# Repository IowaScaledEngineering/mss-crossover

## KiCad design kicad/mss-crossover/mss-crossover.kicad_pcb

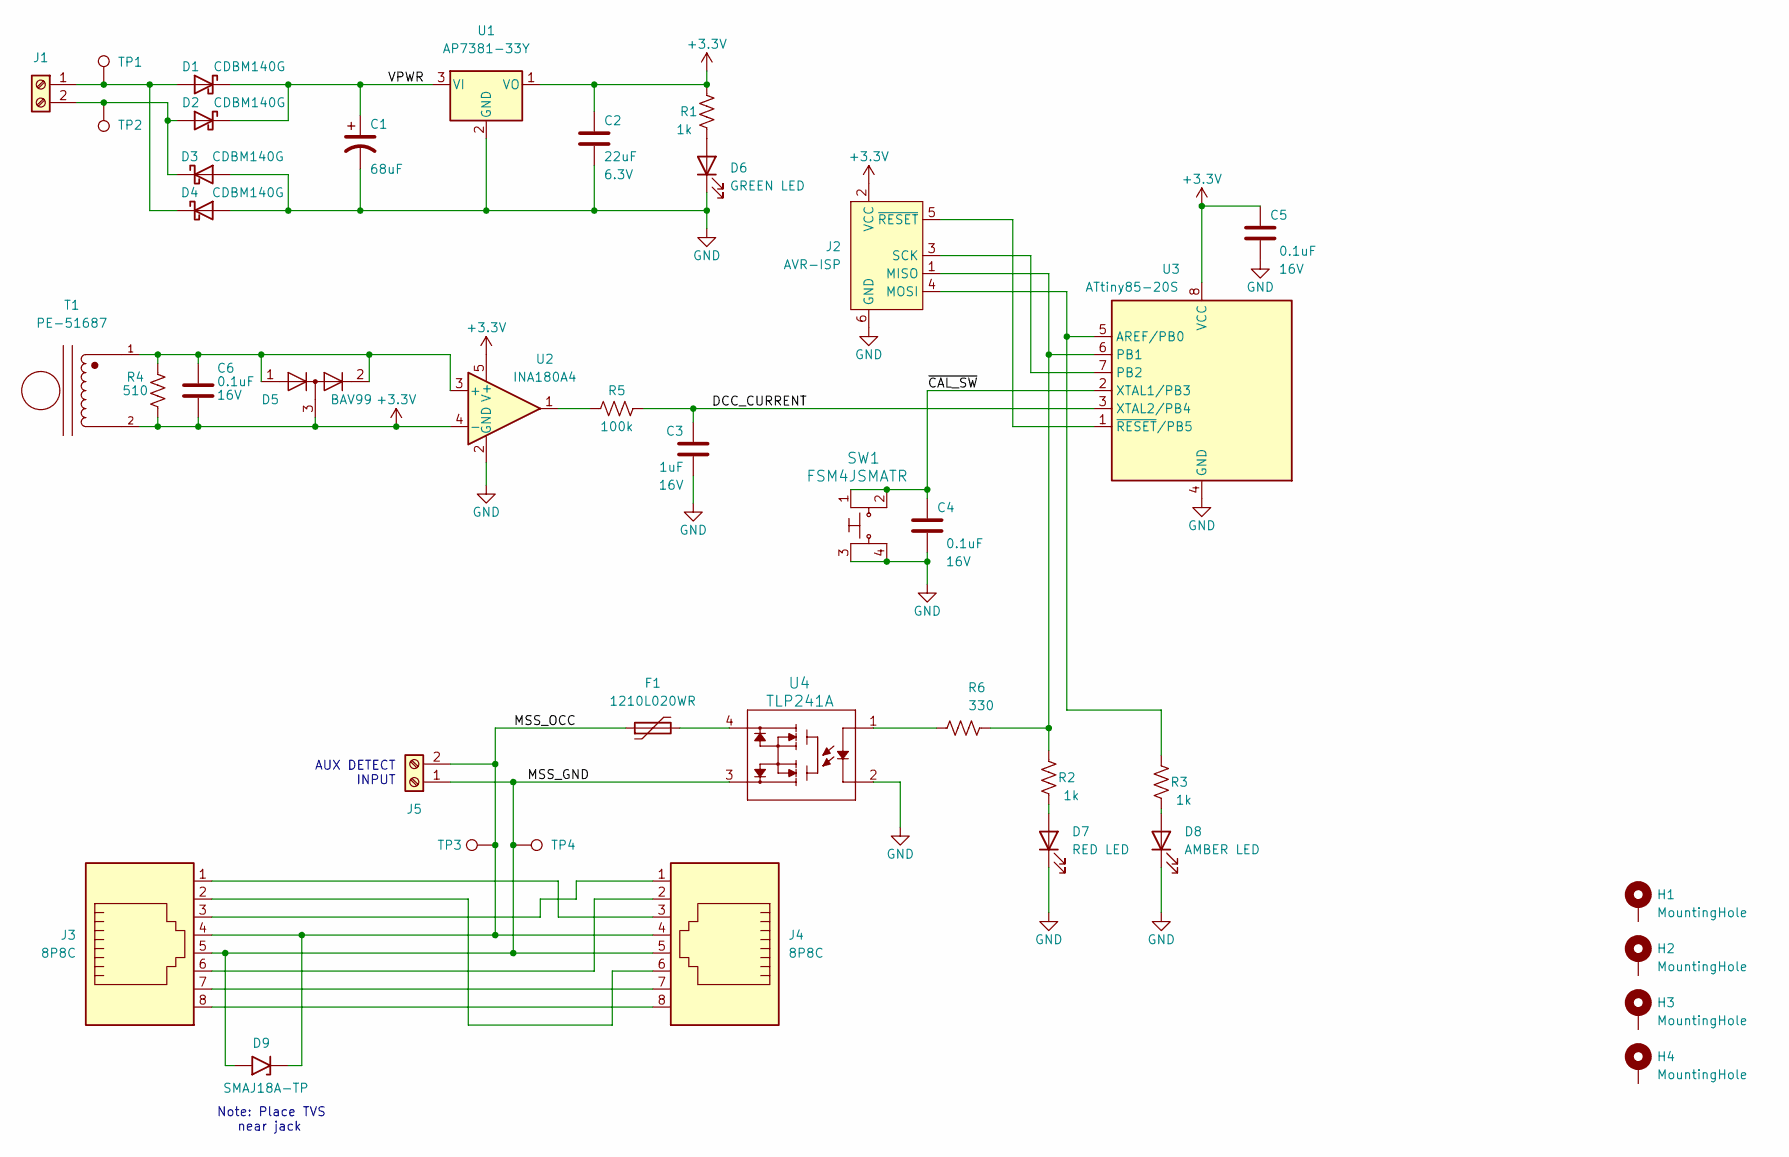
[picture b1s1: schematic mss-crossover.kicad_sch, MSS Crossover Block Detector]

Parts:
C1: 68uF; CP_Elec_6.3x5.8
C2: 22uF; C_0805_2012Metric; Voltage 6.3V
C3: 1uF; C_0805_2012Metric; Voltage 16V
C4, C5, C6: 0.1uF; C_0805_2012Metric; Voltage 16V
D1, D2, D3, D4: CDBM140G; SOD-123T
D5: BAV99; SOT-23
D6: GREEN LED; LED_0805_2012Metric
D7: RED LED; LED_0805_2012Metric
D8: AMBER LED; LED_0805_2012Metric
D9: SMAJ18A-TP; D_SMA
F1: 1210L020WR; R_1210_3225Metric
H1, H2, H3, H4: MountingHole; MountingHole_3.2mm_M3_Pad
J1, J5: Screw_Terminal_01x02; TerminalBlock_RND_205-00012_1x02_P5.00mm_Horizontal
J2: AVR-ISP; Tag-Connect_TC2030-IDC-NL_2x03_P1.27mm_Vertical
J3, J4: 8P8C; RJ45_Amphenol_54602-x08_Horizontal
R1, R2, R3: 1k; R_0805_2012Metric
R4: 510; R_0805_2012Metric
R5: 100k; R_0805_2012Metric
R6: 330; R_0805_2012Metric
SW1: FSM4JSMATR; TE_FSM4JSMA; MPN FSM4JSMATR; Digi-Key_PN 450-1759-1-ND
T1: PE-51687; XFMR_PE-51687
TP1, TP2, TP3, TP4: TestPoint; TestPoint_Pad_D2.0mm
U1: AP7381-33Y; SOT-89-3
U2: INA180A4; SOT-23-5
U3: ATtiny85-20S; ATMEL_SO8_DUAL
U4: TLP241A; 11-5B201S_TOS

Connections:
+3.3V: C2.1, C5.1, C6.2, D5.3 (K), J2.2 (VCC), R1.2, R4.1, T1.2, U1.1 (VO), U2.4 (-), U2.5 (V+), U3.8 (VCC)
/DCC_CURRENT: C3.1, R5.1, U3.3 (XTAL2/PB4)
/MSS_GND: D9.2 (A2), J3.5, J4.5, J5.1, TP4.1, U4.3
/MSS_OCC: D9.1 (A1), F1.1, J3.4, J4.4, J5.2, TP3.1
/VPWR: C1.1, D1.1 (K), D2.1 (K), U1.3 (VI)
/~CAL_SW: C4.1, SW1.1, SW1.2, U3.2 (XTAL1/PB3)
GND: C1.2, C2.2, C3.2, C4.2, C5.2, D3.2 (A), D4.2 (A), D6.1 (K), D7.1 (K), D8.1 (K), J2.6 (GND), SW1.3, SW1.4, U1.2 (GND), U2.2 (GND), U3.4 (GND), U4.2
unnamed: C6.1, D5.1 (K), D5.2 (A), R4.2, T1.1, U2.3 (+)
unnamed: D1.2 (A), D4.1 (K), J1.1, TP1.1
unnamed: D2.2 (A), D3.1 (K), J1.2, TP2.1
unnamed: D6.2 (A), R1.1
unnamed: D7.2 (A), R2.2
unnamed: D8.2 (A), R3.2
unnamed: F1.2, U4.4
unnamed: J2.1 (MISO), R2.1, R6.2, U3.6 (PB1)
unnamed: J2.3 (SCK), U3.7 (PB2)
unnamed: J2.4 (MOSI), R3.1, U3.5 (AREF/PB0)
unnamed: J2.5 (~RESET), U3.1 (~RESET/PB5)
unnamed: J3.1, J4.3
unnamed: J3.2, J4.6
unnamed: J3.3, J4.1
unnamed: J3.6, J4.2
unnamed: J3.7, J4.7
unnamed: J3.8, J4.8
unnamed: R5.2, U2.1
unnamed: R6.1, U4.1

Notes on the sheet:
AUX DETECT INPUT
Note: Place TVS near jack

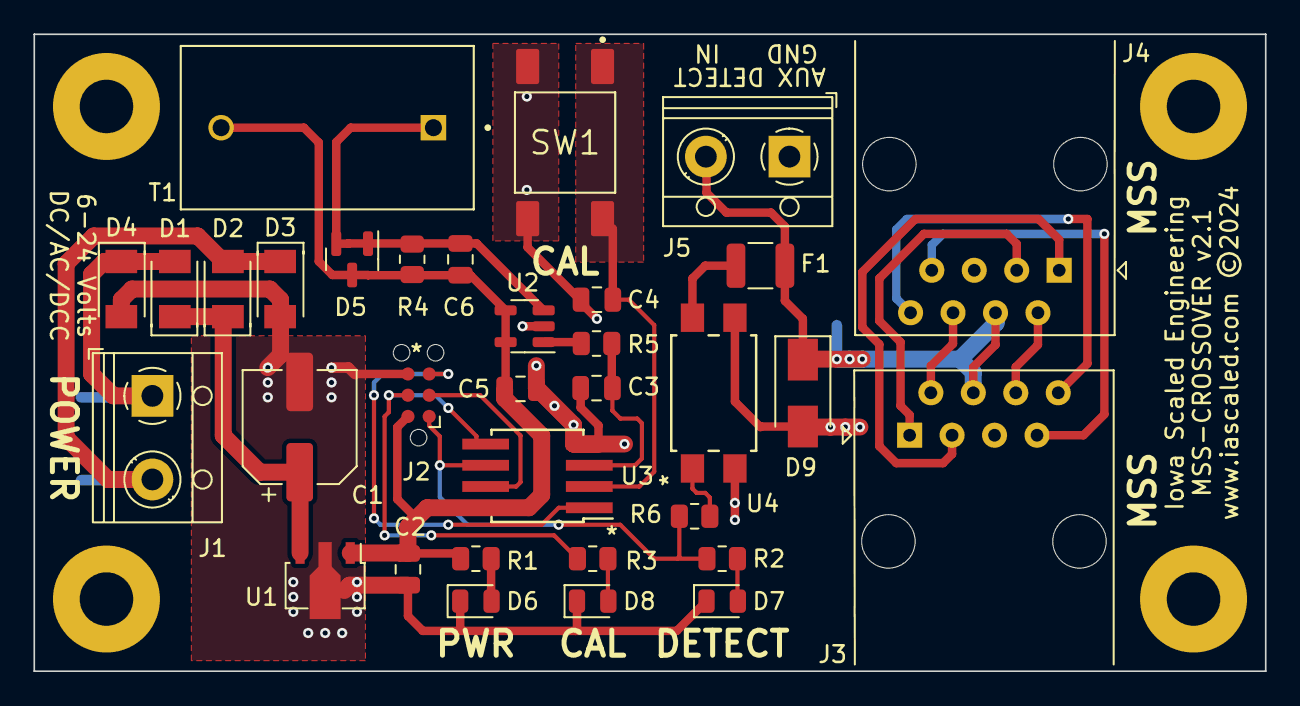
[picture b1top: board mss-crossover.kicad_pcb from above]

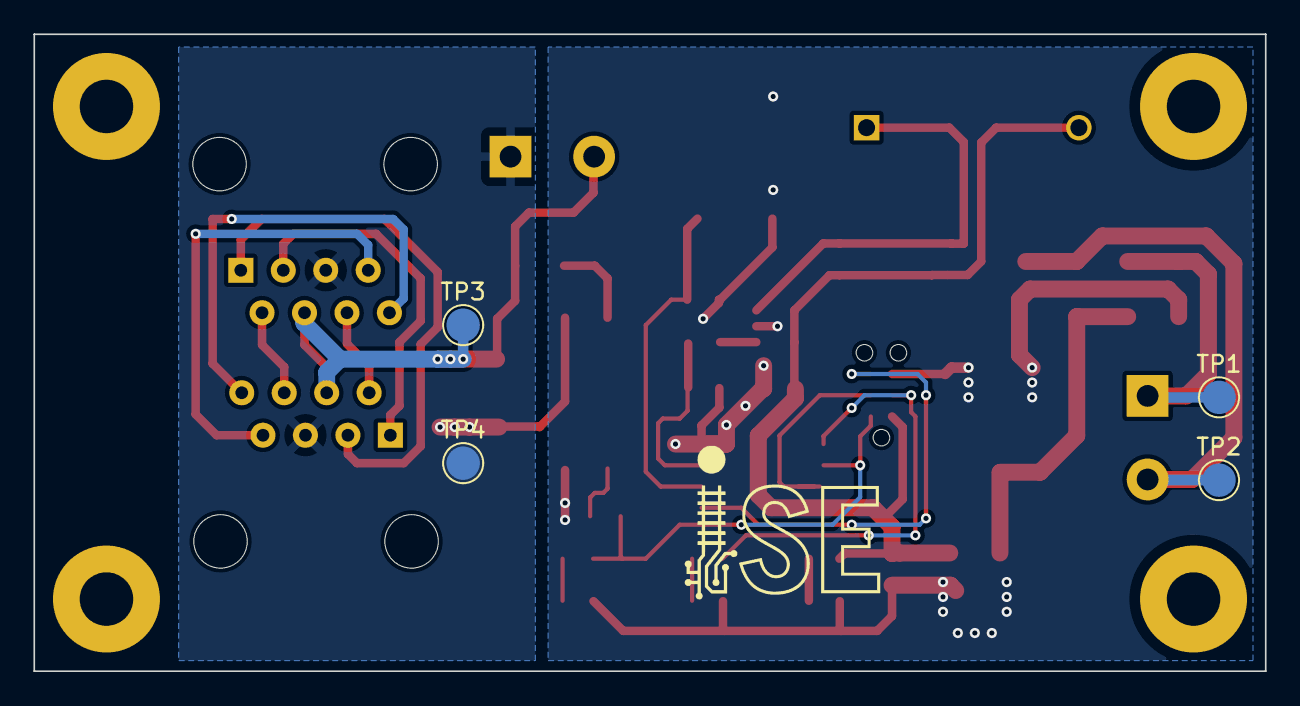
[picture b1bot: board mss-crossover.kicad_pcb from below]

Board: 2 copper layers, 73.7 x 38.1 mm, 41 parts (4 on the bottom side), 26 nets.

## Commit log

2015-10-14 Initial cut of mss-crossover module
2015-10-14 Add licensing, update gitignore
2015-10-14 Update text on schematic
2015-10-27 Change micro, add occupancy input (for turnouts, etc.) and clean up a few things
2015-10-28 First cut of "finished" pcb
2015-10-28 Update occupancy input pullup resistor value
2015-10-28 Twiddling with refdes cleanup and other last minute stuff
2015-11-02 Fix a few things from Michael's review.
2015-11-02 Remove a tiny metal sliver
2015-11-03 Add sensitivity adjustment guide text
2015-11-03 PG v1.0
2015-11-20 Add src
2015-11-21 Diagram for user manual
2015-11-21 Removed extraneous wires
2015-11-21 Add preliminary manual work
2015-11-21 First attempt
2015-11-22 Add blink on aux input functionality
2015-11-22 Reverse light pin definitions
2015-11-23 Change to read delays from eeprom and update if needed
2015-11-24 More manual editing
2015-11-24 Suggestions from Gregg F: - clamp on the aux input - jumper MSS bus 7 to MSS ground, allowing for use as an alternate function
2015-11-24 Modify schematic to add comment Modify PCB to add JP1 and Q2
2015-11-25 Move R10 to the back side of the protection fet to inhibit backfeeding into the power rail
2016-02-26 Add documentation about JP1
2016-03-01 Fix a few things in the manual and make it 1.0
2016-03-06 Make the 1Hz blink actually 1Hz
2016-03-06 Update gitignore to ignore build intermediates
2016-09-14 Change out input protection circuit for a new one.
2016-09-14 Fix a bit of missing metal plane in lower right
2016-09-14 Add schottky symbol
2016-09-14 Combine R6/R9 into 100k 2-pack
2016-09-17 Add crossover v1.1
2017-06-02 Decreased solder paste aperature on the QFN32 footprint. Bumped rev to 1.2 Changed (C) to 2017
2017-06-02 Decreased QFN paste aperture
2017-06-15 Added bag top
2017-09-12 Added new ISE logo.
2018-12-13 Potential v1.3 candidate - improved detector, some other simplifications
2018-12-27 Add pushbutton for DCC current auto-set
2018-12-30 Sent to Seeed
2019-01-14 Fix slot attributes
2019-04-04 New firmware for pushbutton current set
2019-04-04 Change the default current value to approximately what a 10k resistor comes up to on my test track
2024-02-15 New MSS-CROSSOVER v2.0 in Kicad
2024-02-17 Initial PCB layout complete on v2.0
2024-02-25 Updates per review
2024-04-03 Add test points
2024-04-03 Add 3d models
2024-04-06 Files for fab
2024-05-20 Update footprints for AVR to allow for both narrow/wide SO8s and footprint for CDBMs to allow for more paste
2024-05-21 Fix dual footprint SO8
2024-05-21 Update schematic footprints from PCB changes
2024-05-21 Remove old source code and schematic/pcb files from geda
2024-05-21 Fix diode spacing to appease McFussyPants
2024-05-24 Add auxilliary detection terminal block
2024-05-26 Move transformer over and center switch to give more finger room Label aux detect terminals for GND and IN
2024-05-29 Add v4.1 array
2024-05-29 PG of mss-crossover v2.1 array
2024-07-02 Removed old MSS documentation
2024-07-02 Updated ignores
2024-08-07 Add crossover blister box insert stl/gcode

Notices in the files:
kicad/mss-crossover/mss-crossover.kicad_pcb:
www.iascaled.com ©2024
